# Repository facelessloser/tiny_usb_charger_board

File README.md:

# tiny_usb_charger_board
tiny_usb_charger_board

Youtube - https://www.youtube.com/watch?v=VJGOwEa-Fwo
Blog post - https://facelesstech.wordpress.com/2020/02/27/attiny-fairy-lights-usb-phone-charger/

New and improved info

Blog post - https://facelesstech.wordpress.com/2021/01/30/pulse-micro-light-paracord-charging-cable-ios/ 
Youtube - https://youtu.be/SMK6h7EhbCA

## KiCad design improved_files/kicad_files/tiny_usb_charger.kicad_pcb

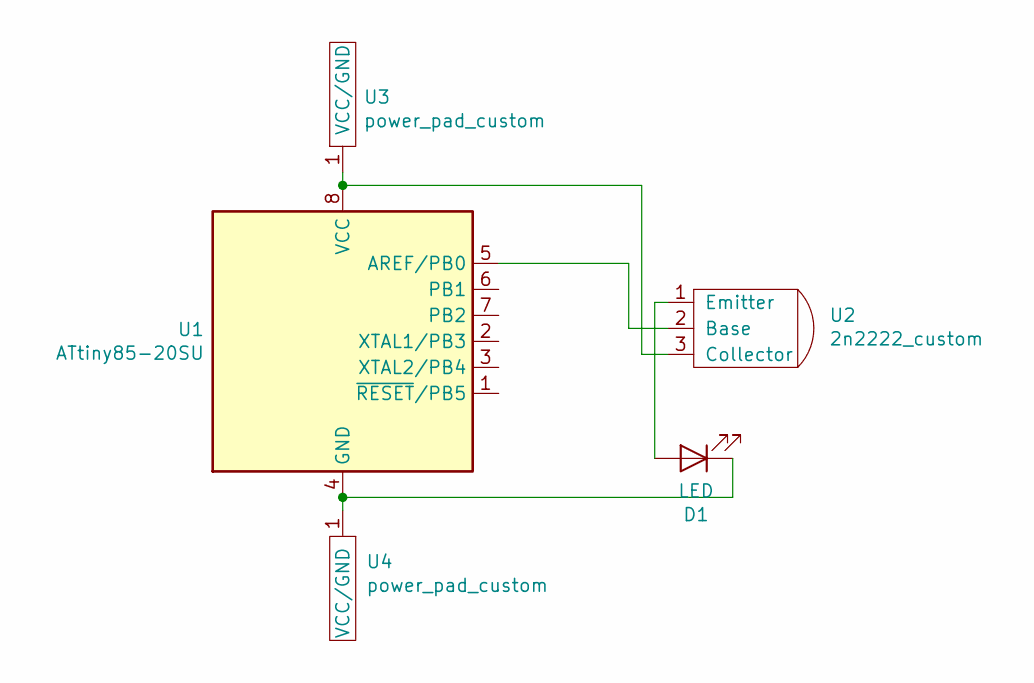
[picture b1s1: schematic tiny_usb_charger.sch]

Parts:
D1: LED; through_hole_led
U1: ATtiny85-20SU; SOIJ-8_5.3x5.3mm_P1.27mm
U2: 2n2222_custom; SOT-23_custom
U3, U4: power_pad_custom

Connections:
unnamed: D1.1 (K), U1.4 (GND), U4.1
unnamed: D1.2 (A), U2.1 (Emitter)
unnamed: U1.5 (AREF/PB0), U2.2 (Base)
unnamed: U1.8 (VCC), U2.3 (Collector), U3.1

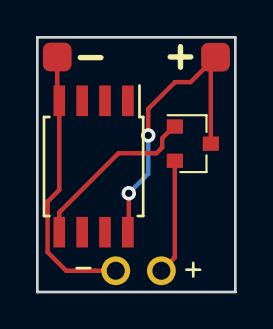
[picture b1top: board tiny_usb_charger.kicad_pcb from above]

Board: 2 copper layers, 11.0 x 14.1 mm, 5 parts (0 on the bottom side), 4 nets.

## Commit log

2020-02-02 3d printing files
2020-02-02 arduino attiny85 files
2020-02-02 removed can file
2020-02-27 added links to readme
2021-01-30 moved files
2021-01-30 new and improved files
2021-01-30 added links
